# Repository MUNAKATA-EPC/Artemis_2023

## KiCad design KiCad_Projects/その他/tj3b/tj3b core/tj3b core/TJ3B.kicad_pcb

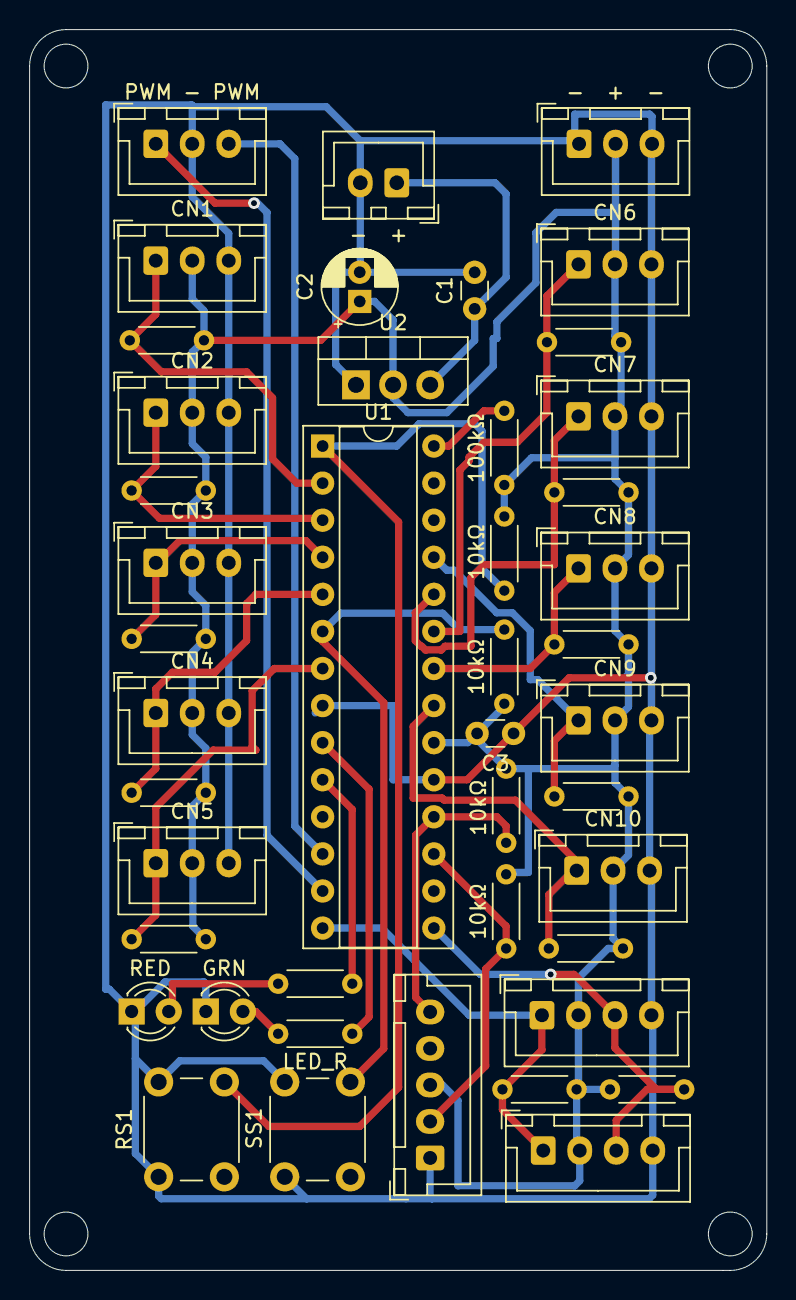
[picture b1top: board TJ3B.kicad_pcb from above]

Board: 2 copper layers, 50.5 x 85.0 mm, 28 parts (0 on the bottom side), 22 nets.

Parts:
10kΩ, 10kΩ#2, 10kΩ#3, 10kΩ#4: R; R_Axial_DIN0204_L3.6mm_D1.6mm_P5.08mm_Horizontal
100kΩ: 100kΩ; R_Axial_DIN0204_L3.6mm_D1.6mm_P5.08mm_Horizontal
-  +: Conn_01x02_Female; JST_XH_B2B-XH-A_1x02_P2.50mm_Vertical
-  +  -: Conn_01x03_Female; JST_XH_B3B-XH-A_1x03_P2.50mm_Vertical
C1, C3: C; C_Disc_D3.0mm_W1.6mm_P2.50mm
C2: C; CP_Radial_D5.0mm_P2.00mm
CN1, CN2, CN3, CN4, CN5, CN6, CN7, CN8, CN9, CN10: Conn_01x03_Female; JST_XH_B3B-XH-A_1x03_P2.50mm_Vertical
GRN: LED; LED_D3.0mm
LED_R: R; R_Axial_DIN0204_L3.6mm_D1.6mm_P5.08mm_Horizontal
PWM - PWM: Conn_01x03_Female; JST_XH_B3B-XH-A_1x03_P2.50mm_Vertical
RED: LED; LED_D3.0mm
RS1: SW_Push; SW_PUSH_6mm
SS1: SW_Push; SW_PUSH_6mm
U1: TJ3_mein; DIP-28_W7.62mm_Socket
U2: AMS1117-1.5; TO-220-3_Vertical

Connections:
+5V: 10kΩ.1, 10kΩ#2.2, 10kΩ#3.1, 10kΩ#4.2, 100kΩ.1, - + -.2, C2.1, C3.2, CN1.2, CN2.2, CN3.2, CN4.2, CN5.2, CN6.2, CN7.2, CN8.2, CN9.2, CN10.2, U1.20, U2.2
AD1: CN1.1, U1.2
AD2: CN2.1, U1.3
AD3: CN3.1, U1.4
AD4: CN4.1, U1.5
AD5: CN5.1, U1.7
AD6: CN6.1, U1.23
AD7: CN7.1, U1.24
AD8: CN8.1, U1.22
AD9: CN9.1, U1.25
AD10: CN10.1, U1.21
GND: - +.2, - + -.1, - + -.3, C1.2, C2.2, C3.1, CN1.3, CN2.3, CN3.3, CN4.3, CN5.3, CN6.3, CN7.3, CN8.3, CN9.3, CN10.3, GRN.1, PWM - PWM.2, RED.1, RS1.2, SS1.2, U1.8, U1.19, U2.1
MCLR: 10kΩ#2.1, RS1.1, U1.1
unnamed: - +.1, C1.1, U2.3
unnamed: GRN.2, LED_R.1
PGD_×: 100kΩ.2, U1.28
PWM1: PWM - PWM.3, U1.12
PWM2: PWM - PWM.1, U1.13
PWR_LED: LED_R.2, U1.9
RA4: 10kΩ.2, SS1.1, U1.6
RX: 10kΩ#3.2, U1.18
TX: 10kΩ#4.1, U1.17

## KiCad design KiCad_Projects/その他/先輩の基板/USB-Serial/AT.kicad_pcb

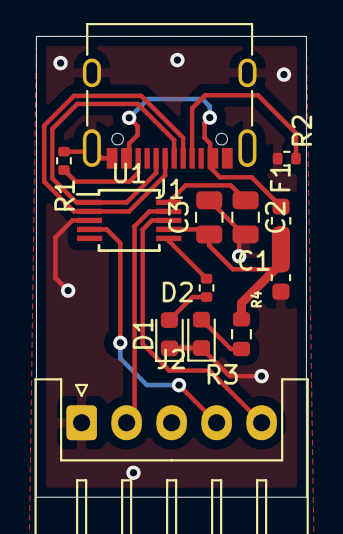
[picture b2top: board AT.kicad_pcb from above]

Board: 2 copper layers, 15.0 x 25.6 mm, 13 parts (0 on the bottom side), 14 nets.

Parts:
C1: C_Small; C_0603_1608Metric
C2, C3: C_Small; C_0805_2012Metric
D1, D2: LED; LED_0603_1608Metric
F1: Fuse; Fuse_0603_1608Metric
J1: USB_C_Receptacle_USB2.0; USB_C_Receptacle_XKB_U262-16XN-4BVC11
J2: Conn_01x05; JST_XH_S5B-XH-A_1x05_P2.50mm_Horizontal
R1, R2, R4: R; R_0402_1005Metric
R3: R; R_0603_1608Metric
U1: CH340E; MSOP-10_3x3mm_P0.5mm

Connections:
GND: C1.2, C2.2, C3.2, D1.1, D2.1, J1.A1, J1.A12, J1.B1, J1.B12, J1.S1, J2.1, R1.1, R2.1, U1.3
unnamed: C2.1, U1.10
unnamed: D1.2, R4.2
unnamed: D2.2, R3.1
unnamed: F1.2, J1.A4, J1.A9, J1.B4, J1.B9
unnamed: J1.A5, R2.2
unnamed: J1.A6, J1.B6, U1.1
unnamed: J1.A7, J1.B7, U1.2
unnamed: J1.B5, R1.2
unnamed: J2.2, U1.9
unnamed: J2.4, U1.4
unnamed: J2.5, U1.8
unnamed: R4.1, U1.6
VCC: C1.1, C3.1, F1.1, R3.2, U1.7

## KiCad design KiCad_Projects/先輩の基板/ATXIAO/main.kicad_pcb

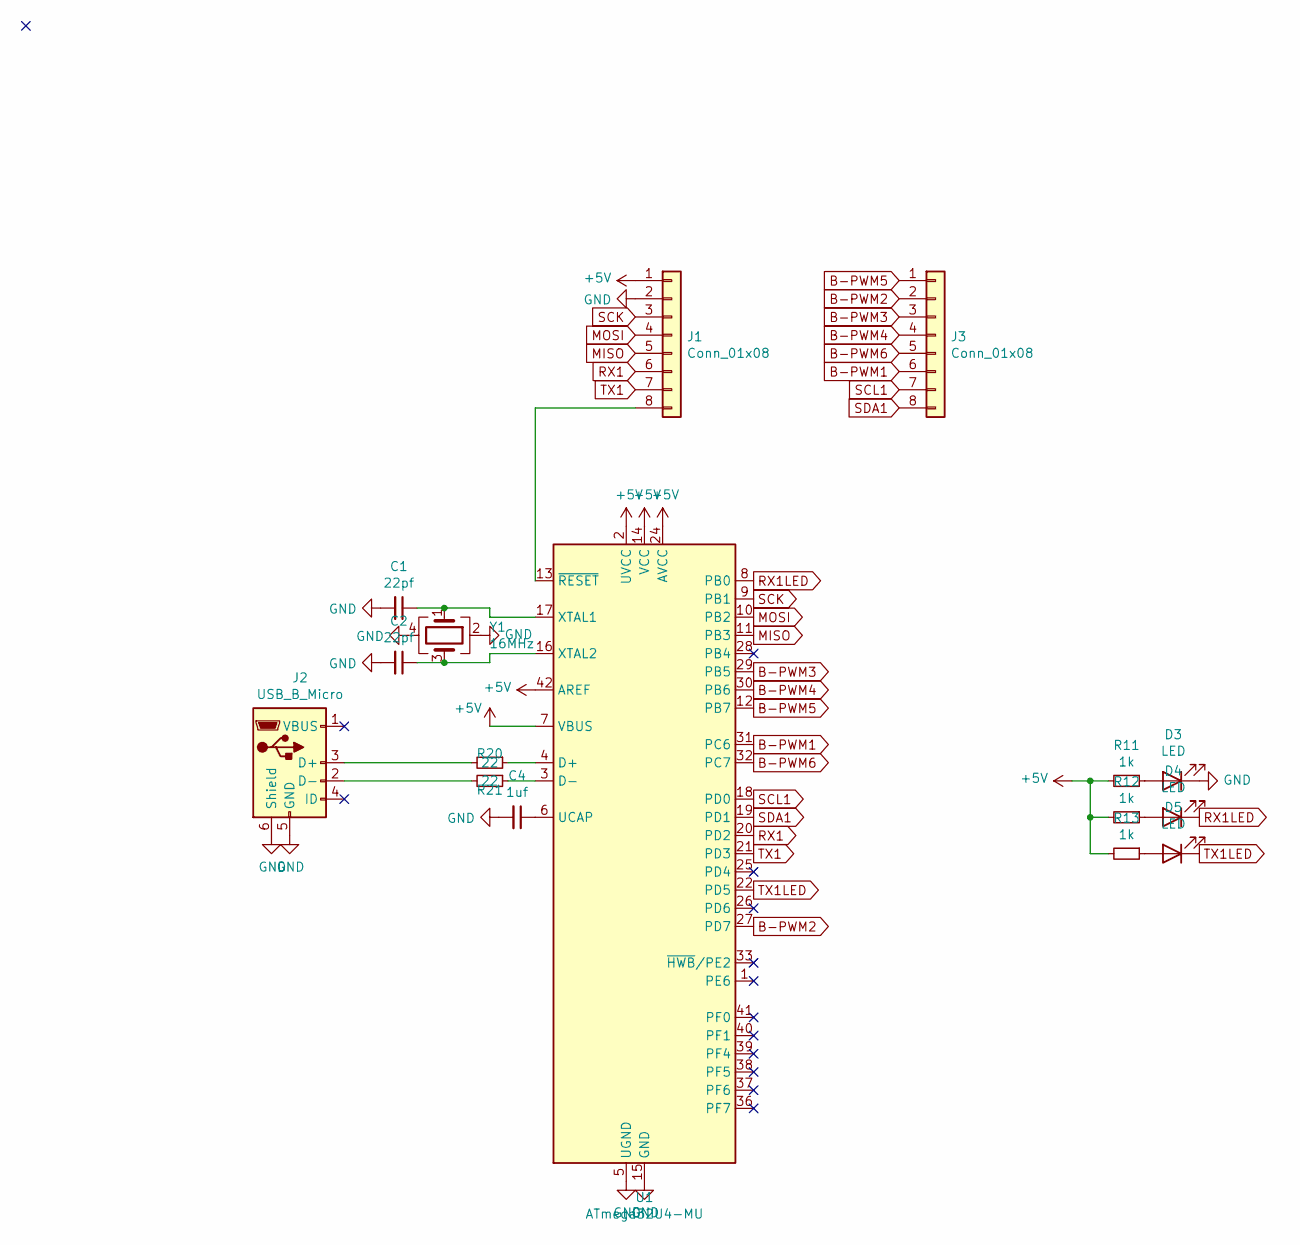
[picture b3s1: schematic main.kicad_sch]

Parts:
C1, C2: 22pf; C_0402_1005Metric; LCSC C1555
C4: 1uf; C_0402_1005Metric; LCSC C52923
D3, D4, D5: LED; LED_0402_1005Metric; LCSC C130725
J1, J3: Conn_01x08; PinHeader_1x08_P2.54mm_Vertical
J2: USB_B_Micro; USB_Micro-B_Molex_47346-0001; LCSC C132560
R11, R12, R13: 1k; R_0402_1005Metric; LCSC C11702
R20, R21: 22; R_0402_1005Metric; LCSC C25092
U1: ATmega32U4-MU; QFN-44-1EP_7x7mm_P0.5mm_EP5.2x5.2mm; LCSC C112161
Y1: 16MHz; Crystal_SMD_3225-4Pin_3.2x2.5mm; LCSC C164049

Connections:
+5V: J1.1, R11.2, R12.2, R13.2, U1.2 (UVCC), U1.7 (VBUS), U1.14 (VCC), U1.24 (AVCC), U1.34 (VCC), U1.42 (AREF), U1.44 (AVCC)
B-PWM1: J3.6, U1.31 (PC6)
B-PWM2: J3.2, U1.27 (PD7)
B-PWM3: J3.3, U1.29 (PB5)
B-PWM4: J3.4, U1.30 (PB6)
B-PWM5: J3.1, U1.12 (PB7)
B-PWM6: J3.5, U1.32 (PC7)
GND: C1.2, C2.2, C4.2, D3.1 (K), J1.2, J2.5 (GND), J2.6 (Shield), U1.5 (UGND), U1.15 (GND), U1.23 (GND), U1.35 (GND), U1.43 (GND), U1.45 (GND), Y1.2, Y1.4
MISO: J1.5, U1.11 (PB3)
MOSI: J1.4, U1.10 (PB2)
unnamed: C1.1, U1.17 (XTAL1), Y1.1
unnamed: C2.1, U1.16 (XTAL2), Y1.3
unnamed: C4.1, U1.6 (UCAP)
unnamed: D3.2 (A), R11.1
unnamed: D4.2 (A), R12.1
unnamed: D5.2 (A), R13.1
unnamed: J1.8, U1.13 (~RESET)
unnamed: J2.2 (D-), R21.2
unnamed: J2.3 (D+), R20.2
unnamed: R20.1, U1.4 (D+)
unnamed: R21.1, U1.3 (D-)
RX1: J1.6, U1.20 (PD2)
RX1LED: D4.1 (K), U1.8 (PB0)
SCK: J1.3, U1.9 (PB1)
SCL1: J3.7, U1.18 (PD0)
SDA1: J3.8, U1.19 (PD1)
TX1: J1.7, U1.21 (PD3)
TX1LED: D5.1 (K), U1.22 (PD5)

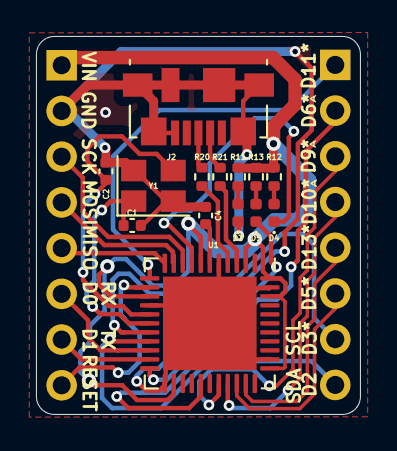
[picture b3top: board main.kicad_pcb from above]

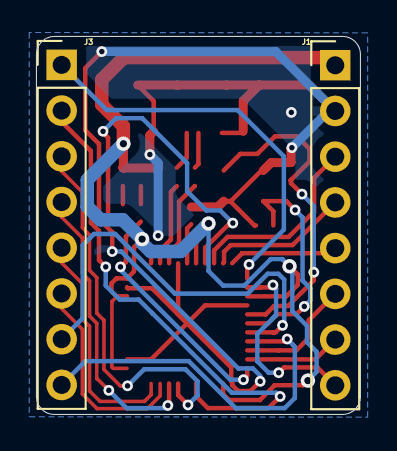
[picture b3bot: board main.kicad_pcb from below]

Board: 2 copper layers, 18.0 x 21.0 mm, 16 parts (2 on the bottom side), 28 nets.
